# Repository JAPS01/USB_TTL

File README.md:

## USB to TTL converter 

USB to TTL converter using ch340c, with a small size and compatible with 5V and 3.3V voltages.

It already has pins for micro reset without having to press the reset button.

## Installation

Install Drivers

You can use sparkfun installation guide for drivers: 
https://learn.sparkfun.com/tutorials/how-to-install-ch340-drivers/all#mac-osx

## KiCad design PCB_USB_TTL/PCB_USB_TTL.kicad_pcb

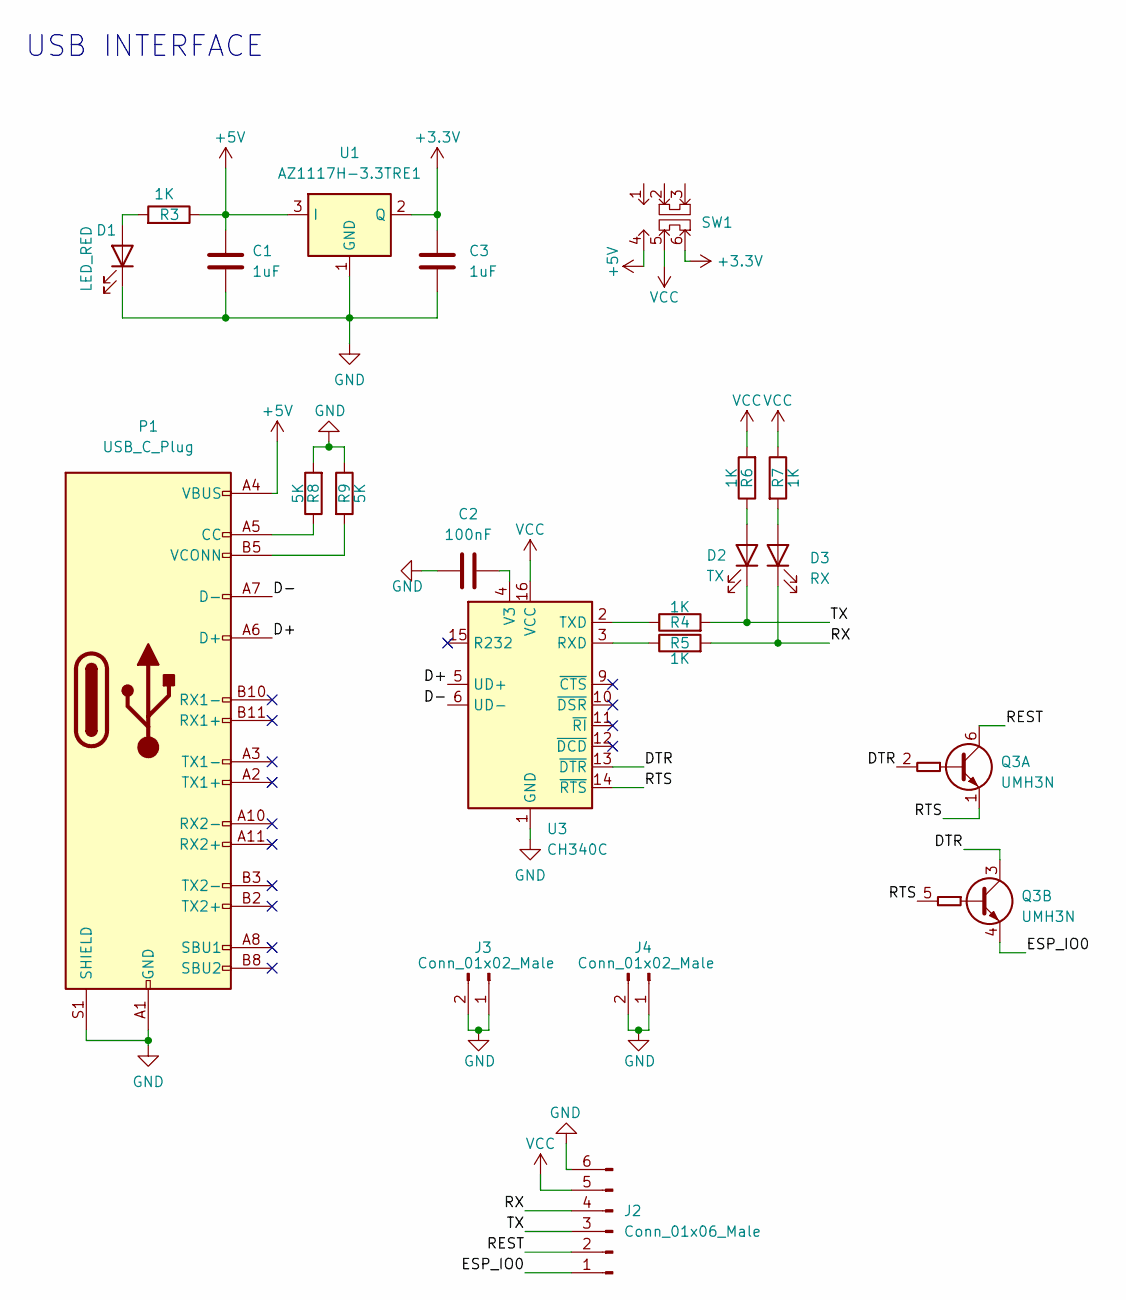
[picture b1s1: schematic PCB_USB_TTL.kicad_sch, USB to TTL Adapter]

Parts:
C1, C3: 1uF; C_1206_3216Metric_Pad1.33x1.80mm_HandSolder
C2: 100nF; C_1206_3216Metric_Pad1.33x1.80mm_HandSolder
D1: LED_RED; LED_1206_3216Metric_Pad1.42x1.75mm_HandSolder
D2: TX; LED_1206_3216Metric_Pad1.42x1.75mm_HandSolder
D3: RX; LED_1206_3216Metric_Pad1.42x1.75mm_HandSolder
J2: Conn_01x06_Male; PinHeader_1x06_P2.54mm_Vertical
J3, J4: Conn_01x02_Male; PinHeader_1x02_P2.54mm_Vertical
P1: USB_C_Plug; USB_C_Receptacle_XKB_U262-16XN-4BVC11
Q3: UMH3N; SOT-363_SC-70-6
R3, R4, R5, R6, R7: 1K; R_1206_3216Metric_Pad1.30x1.75mm_HandSolder
R8, R9: 5K; R_1206_3216Metric_Pad1.30x1.75mm_HandSolder
SW1: MS-22D28-G020
U1: AZ1117H-3.3TRE1; SOT-223
U3: CH340C; SOIC-16_3.9x9.9mm_P1.27mm

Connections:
+3.3V: C3.1, SW1.6, U1.2 (Q)
+5V: C1.1, P1.A4 (VBUS), P1.A9 (VBUS), P1.B4 (VBUS), P1.B9 (VBUS), R3.1, SW1.4, U1.3 (I)
/D+: P1.A6 (D+), U3.5 (UD+)
/D-: P1.A7 (D-), U3.6 (UD-)
/DTR: Q3.2 (B1), Q3.3 (C2), U3.13 (~DTR)
/ESP_IO0: J2.1, Q3.4 (E2)
/REST: J2.2, Q3.6 (C1)
/RTS: Q3.1 (E1), Q3.5 (B2), U3.14 (~RTS)
/RX: D3.1 (K), J2.4, R5.2
/TX: D2.1 (K), J2.3, R4.2
GND: C1.2, C2.1, C3.2, D1.1 (K), J2.6, J3.1, J3.2, J4.1, J4.2, P1.A1 (GND), P1.A12 (GND), P1.B1 (GND), P1.B12 (GND), P1.S1 (SHIELD), R8.2, R9.1, U1.1 (GND), U3.1 (GND)
unnamed: D1.2 (A), R3.2
unnamed: D2.2 (A), R6.1
unnamed: D3.2 (A), R7.2
unnamed: P1.A5 (CC), R8.1
unnamed: P1.B5 (VCONN), R9.2
unnamed: R5.1, U3.3 (RXD)
unnamed: R4.1, U3.2 (TXD)
unnamed: C2.2, U3.4 (V3)
VCC: J2.5, R6.2, R7.1, SW1.5, U3.16 (VCC)

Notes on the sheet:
USB INTERFACE

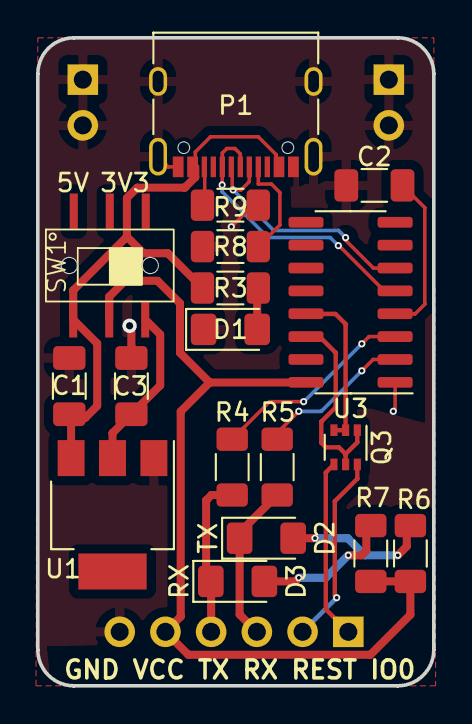
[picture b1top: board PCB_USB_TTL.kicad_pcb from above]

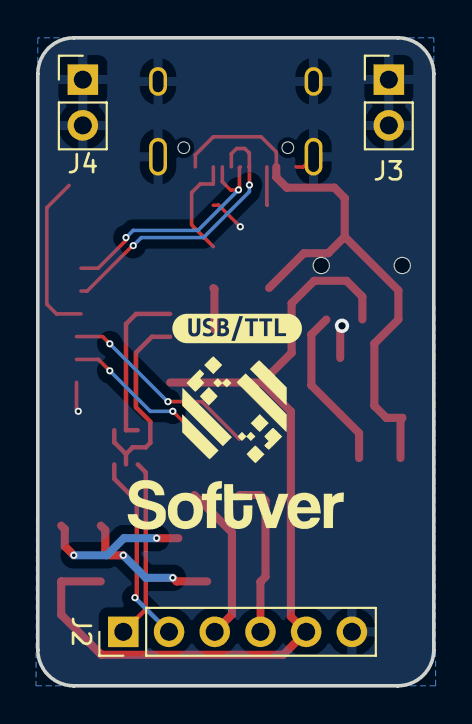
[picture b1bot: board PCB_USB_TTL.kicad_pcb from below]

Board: 2 copper layers, 22.0 x 36.0 mm, 22 parts (4 on the bottom side), 20 nets.

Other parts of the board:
kibuzzard-638F54F7: G***; kibuzzard-638F54F7

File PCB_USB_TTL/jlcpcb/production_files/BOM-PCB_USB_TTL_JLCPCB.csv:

Comment,Designator,Footprint,LCSC
1K,"R3,R4,R5,R6,R7",R_1206_3216Metric_Pad1.30x1.75mm_HandSolder,C112223
UMH3N,Q3,SOT-363_SC-70-6,C123008
5K,"R8,R9",R_1206_3216Metric_Pad1.30x1.75mm_HandSolder,C136458
USB_C_Plug,P1,USB_C_Receptacle_XKB_U262-16XN-4BVC11,C319148
1uF,"C1,C3",C_1206_3216Metric_Pad1.33x1.80mm_HandSolder,C326607
100nF,C2,C_1206_3216Metric_Pad1.33x1.80mm_HandSolder,C82601
CH340C,U3,SOIC-16_3.9x9.9mm_P1.27mm,C84681
AZ1117H-3.3TRE1,U1,SOT-223,C92517
~,SW1,MS-22D28-G020,C963205
LED_RED,D1,LED_1206_3216Metric_Pad1.42x1.75mm_HandSolder,C965822
TX,"D2,D3",LED_1206_3216Metric_Pad1.42x1.75mm_HandSolder,C965826

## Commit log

2023-04-05 PCB using CH340C
2023-05-23 Rev 2
    Switch is added to change from 3.3v to 5v.
    UMH3N is used to save space and cost.
2023-05-23 Rev 2
    Add renders
2023-05-23 update renders file
